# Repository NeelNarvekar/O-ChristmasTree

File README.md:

# O-ChristmasTree
ECE 3872 Project

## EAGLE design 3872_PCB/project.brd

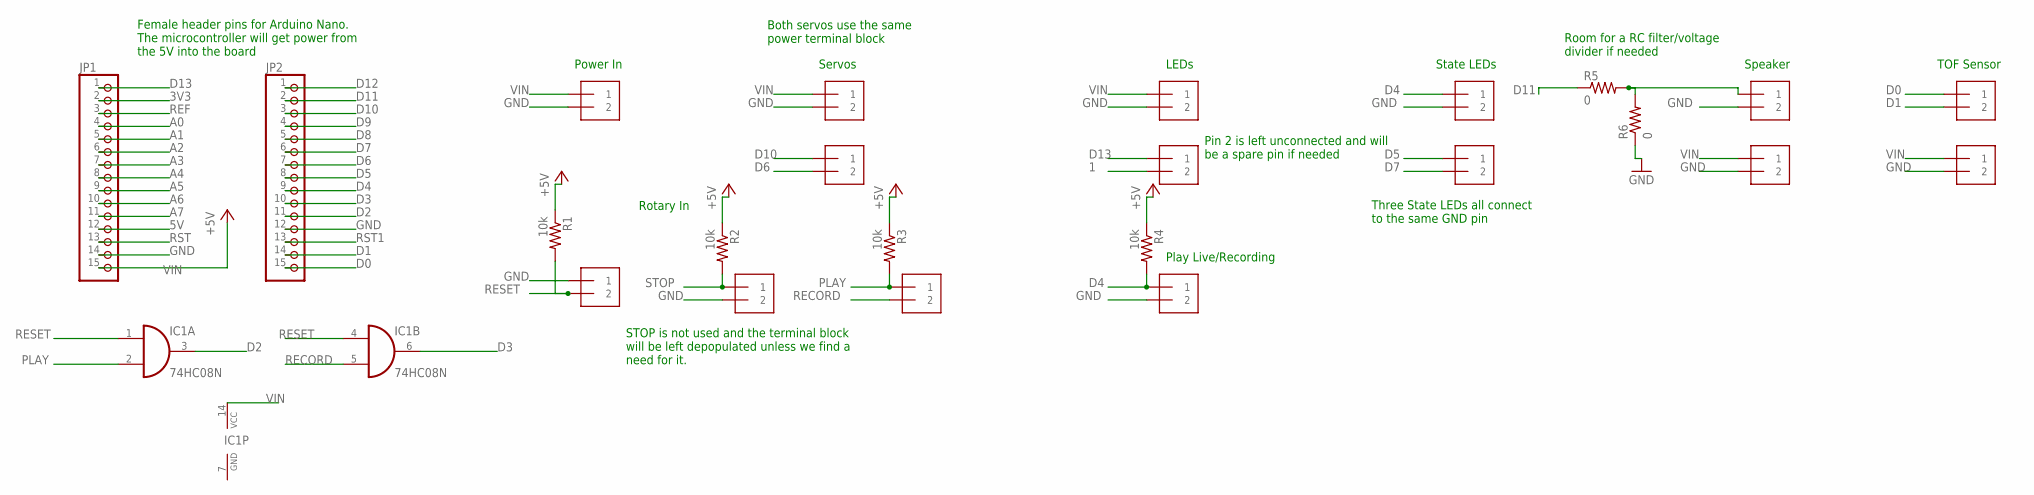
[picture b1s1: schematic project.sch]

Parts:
IC1: 74HC08N; DIL14
J1, J2, J3, J4: 1X2-3.5MM
JP1, JP2: PINHD-1X15; 1X15
LED1, LED2_3: 1X2-3.5MM
LED_PWR: 1X2-3.5MM
LED_SIG: 1X2-3.5MM
POWER: 1X2-3.5MM
R1, R2, R3, R4: 10k; M0805
R5, R6: 0; M0805
SERVO_PWR: 1X2-3.5MM
SERVO_SIG: 1X2-3.5MM
SPK_PWR: 1X2-3.5MM
SPK_SIG: 1X2-3.5MM
TOF_PWR: 1X2-3.5MM
TOF_SIG: 1X2-3.5MM

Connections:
1: LED_SIG.2
3V3: JP1.2
5V: JP1.12
A0: JP1.4
A1: JP1.5
A2: JP1.6
A3: JP1.7
A4: JP1.8
A5: JP1.9
A6: JP1.10
A7: JP1.11
D0: JP2.15, TOF_SIG.1
D1: JP2.14, TOF_SIG.2
D2: IC1.3 (O), JP2.11
D3: IC1.6 (O), JP2.10
D4: J1.1, JP2.9, LED1.1, R4.2
D5: JP2.8, LED2_3.1
D6: JP2.7, SERVO_SIG.2
D7: JP2.6, LED2_3.2
D8: JP2.5
D9: JP2.4
D10: JP2.3, SERVO_SIG.1
D11: JP2.2, R5.1
D12: JP2.1
D13: JP1.1, LED_SIG.1
GND: IC1.7 (GND), J1.2, J3.2, J4.1, JP1.14, JP2.12, LED1.2, LED_PWR.2, POWER.2, R6.1, SERVO_PWR.2, SPK_PWR.2, SPK_SIG.2, TOF_PWR.2
unnamed: R5.2, R6.2, SPK_SIG.1
PLAY: IC1.2 (I1), J2.1, R3.2
RECORD: IC1.5 (I1), J2.2
REF: JP1.3
RESET: IC1.1 (I0), IC1.4 (I0), J4.2, R1.2
RST: JP1.13
RST1: JP2.13
STOP: J3.1, R2.2
VIN: IC1.14 (VCC), JP1.15, LED_PWR.1, POWER.1, R1.1, R2.1, R3.1, R4.1, SERVO_PWR.1, SPK_PWR.1, TOF_PWR.1

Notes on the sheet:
State LEDs
Servos
LEDs
Power In
Rotary In
Play Live/Recording
Speaker
TOF Sensor
Female header pins for Arduino Nano. The microcontroller will get power from the 5V into the board
STOP is not used and the terminal block will be left depopulated unless we find a need for it.
Both servos use the same power terminal block
Pin 2 is left unconnected and will be a spare pin if needed
Three State LEDs all connect to the same GND pin
Room for a RC filter/voltage divider if needed

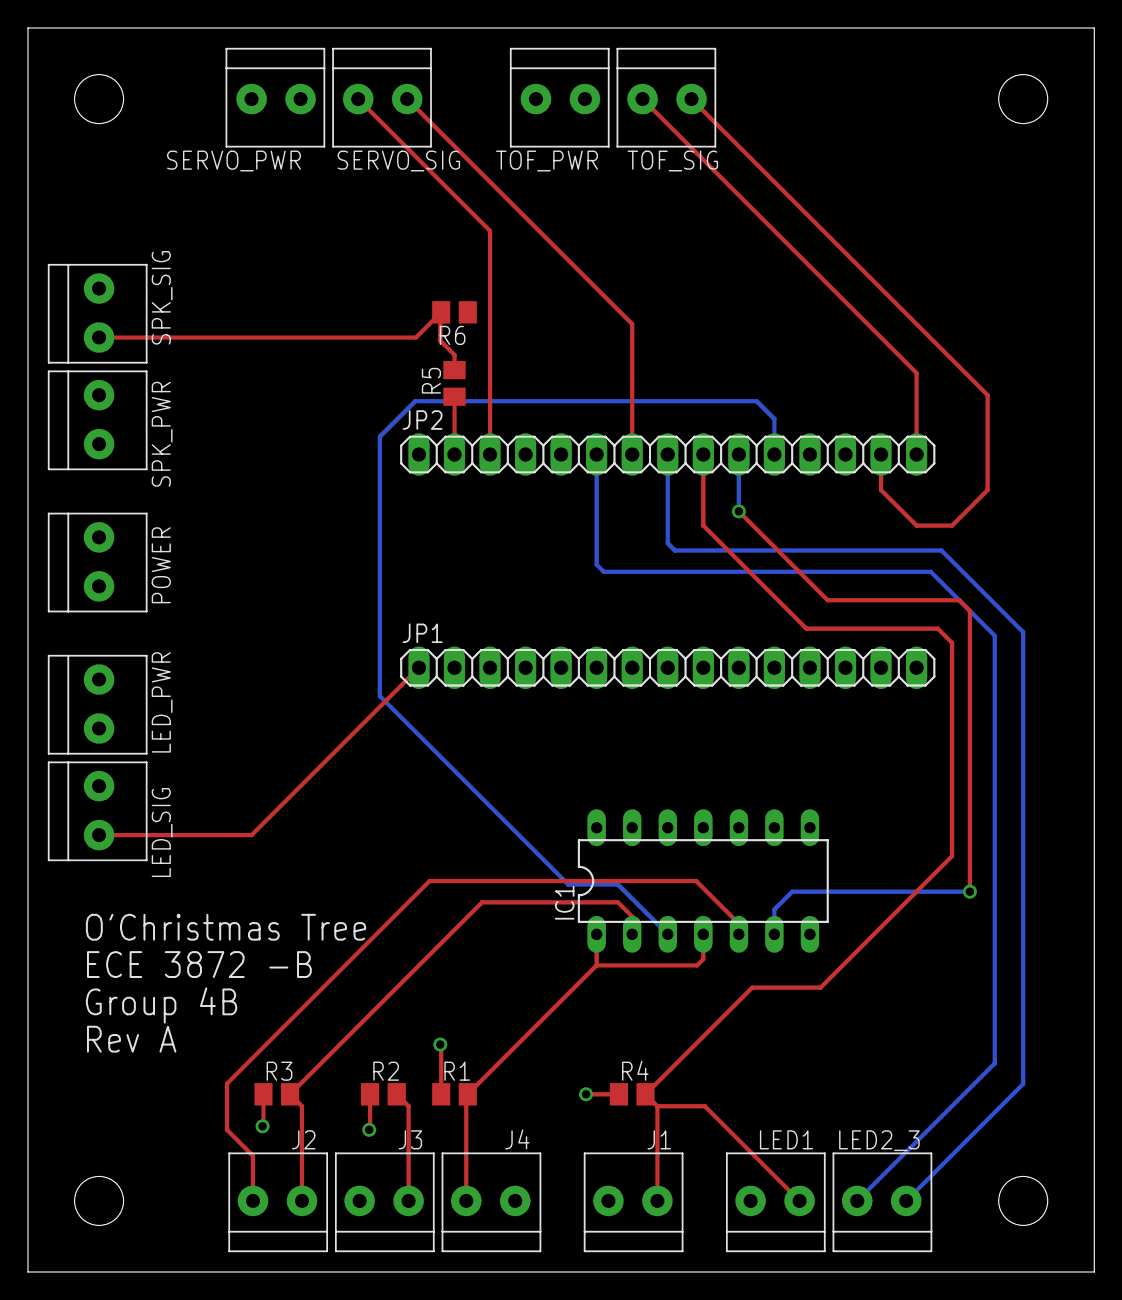
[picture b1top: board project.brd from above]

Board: 2 copper layers, 76.2 x 88.9 mm, 24 parts (0 on the bottom side), 18 nets.

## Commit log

2020-09-18 State Machine for Christmas Tree Project
2020-09-18 Removing folder
2020-09-18 Changing Interrupts to 2 pin design
2020-09-18 Pushed wrong file
2020-09-21 Combined play functions, defining tasks
2020-09-21 Updated global data structures, function API, recording
2020-09-23 Updated code to work with simulator
2020-09-24 Updated audio recording and playback, added bins for 12 notes
2020-09-25 added servo moving and led lighting functionality
2020-09-25 Changed recording for simulation, minor print and other changes
2020-09-25 Working simulator for 12 notes
2020-09-25 Fixing recording functionality
2020-09-25 Merged changes from Connor and Neel
2020-09-25 Updating play pin to stop pin based on interrupt changes
2020-09-26 Commenting code
2020-09-26 Minor revision with comments
2020-10-01 CAD File Parts
2020-10-02 Added inner teeth to each ring
    yeet
2020-10-02 Adding the PCB project
2020-10-02 Assembly
    gears attached
2020-10-02 Updated CAD Files
2020-10-09 Completed board layout and ran the cam outputs to produce gerber and drill files
2020-10-09 Added Arduino simulation file for other testing
2020-10-09 CAD Parts, Axle design changed to be modular
    Axle now has resting disk for each of the rings. Modular design to allow putting on rings.
2020-10-11 Added annotations to the schematic and added a power connection to the quad AND gate IC and regenerated Gerber/drill files
2020-10-15 Gears added to allow for movement
2020-10-15 Updated Arduino testing for Sonar and Servo
2020-10-19 Updated source code to account for sonar input
2020-10-22 Removed state machine call from state functions to prevent overflow
2020-10-23 Update timing on main file and working speaker/sonar/servo sim on test
2020-10-28 Began code to read sonar directly to note instead of frequency, unfinished
2020-10-30 Testing code works with all devices, working on Play Live state in actual file
2020-11-02 Working demo code without Serial monitor, added timing for Record state, and Reset zeros the play index
2020-11-05 Futher code updates for LEDs and cleanup
2020-11-06 Reduced servo range to 35-145, both servos go in an opposite direction
2020-11-06 Changed lighting profile and accounted for the reduced number of LEDs
2020-11-07 Final commit - cleanup
2020-11-09 Final CAD Models.
